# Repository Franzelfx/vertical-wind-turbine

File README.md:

# Vertical wind turbine

A small 3D-printed vertical-axis turbine on a timber post, charging a 3S Li-ion pack (the usual "12 V")
through its own electronics in a weatherproof box. Every part is generated by scripts from one file of
numbers.

> [!NOTE]
> **Digital design only.** The enclosure and drive train are modelled and pass collision checks. The
> schematic passes ERC, and the board is placed but not routed. There is no firmware. Nothing is built, and
> every power figure is an estimate. Next steps are in [plans/](plans/README.md).

<p align="center">
  
</p>

## What to expect

This is a project to enjoy, not an energy source.

<!-- vawt:key-figures:start -->
| Figure | Value |
| --- | --- |
| Rotor | 245 x 890 mm, printed in ASA |
| Post | 80 x 80 mm timber, 3 m tall |
| Battery | 3S2P Li-ion, 76 Wh, 9.0-12.6 V |
| Charges in winds of | 2.8 to 17.1 m/s |
| Best output | 19.1 W, at 17 m/s |
| Average output | 0.43 W at an assumed 3.5 m/s mean wind: 3.8 kWh a year |
| A 20 W solar panel, for scale | about 19 kWh a year |
| Requirements | 23 of 23 hold, on paper |
<!-- vawt:key-figures:end -->

Treat power figures as ±50 % until bench tests replace the assumptions: see
[sizing](docs/sizing.md), [assumptions](docs/assumptions.md) and [bench tests](plans/bench.md).

## How it works

```mermaid
flowchart LR
    wind([Wind]) --> rotor[Printed rotor]
    rotor --> generator[Gimbal motor<br/>as generator]
    generator --> guard[Bridge and<br/>overvoltage relay]
    guard --> charger[BQ25798<br/>charger]
    charger --> pack[(3S Li-ion<br/>pack)]
    pack --> load([Your load])
    mcu[ESP32-C3] -. tracks the best point .-> charger
```

The relay needs no battery and no firmware: the overvoltage itself opens it
([ADR-006](docs/decisions/ADR-006-overvoltage-relay.md)).

## Pictures

All are computer renders, and the garden is set dressing. Select one for full size.

| On its post | From the side | The rotor from below |
| --- | --- | --- |
|  |  |  |

| Upper bracket | Drive train | Cover off |
| --- | --- | --- |
|  |  |  |

| Enclosure | Inside | Exploded |
| --- | --- | --- |
|  |  |  |

## Documentation

| Page | What it holds |
| --- | --- |
| [Requirements](plans/requirements.md) | Numbered limits and where each stands |
| [Sizing](docs/sizing.md) | Power, yield, overvoltage, stopping, structure, vibration |
| [Assumptions](docs/assumptions.md) | Every number nobody has measured |
| [Hardware](docs/hardware.md), [printing](docs/printing.md), [board parts](docs/bom.md) | What to buy and print |
| [Schematic](docs/images/charge-board-schematic.pdf) | The charge board, as a PDF |
| [Decisions](docs/README.md#decisions) | Why it is the way it is, including which choices were made by AI |
| [Plans](plans/README.md) | Mechanical, electronics and bench tests, with what is done |

## Layout

```text
src/vawt/          spec.py: every number. system/: sizing, requirements. io/: docs, booklet, meshes
cad/freecad/       The parts and assembly, as FreeCAD Python
cad/vendor/        The licensed rotor, not in git
electronics/       KiCad: charge-board/ with its schematic as code, lib/ with project parts
firmware/          ESP32-C3, not started
tools/             run-checks, build-cad, build-electronics, render
report/            The booklet's text and layout, as Typst
tests/             Requirements, CAD report, ERC and DRC, doc integrity
plans/             Intent: requirements, mechanical, electronics, bench tests
docs/              State: generated pages, decisions, images
datasheets/        Parts' datasheets
bench/runs/        Raw logs from physical tests
build/             Generated: STEP, STL, FCStd, reports. Not committed
```

## Use

Needs [`uv`](https://docs.astral.sh/uv/), FreeCAD 1.1, KiCad 10 and Blender, each in its default place or
named by an environment variable ([CLAUDE.md](CLAUDE.md)). Git LFS holds the full-size renders and PDFs. For
the CAD build, put the rotor's 3MF in `cad/vendor/ugrinsky/` ([how](cad/vendor/ugrinsky/README.md)).

```sh
uv run vawt sizing          # the figures
tools/run-checks.sh         # everything, about 90 s
tools/render.sh             # the pictures, about 10 minutes (--samples 32 --width 800 for a draft)
uv run vawt pdf             # the booklet for friends: build/report/vertical-wind-turbine.pdf
```

Afterwards, `build/cad/wind-turbine.FCStd` opens in FreeCAD, `build/cad/` holds each part's STEP and STL, and
`electronics/charge-board/charge-board.kicad_pro` opens in KiCad. In FreeCAD, run
`cad/freecad/apply_colours.py` to colour the assembly. Change parts in the scripts, not in the generated
files ([ADR-001](docs/decisions/ADR-001-tools.md)).

## Safety

> [!WARNING]
> This has not been built, tested or certified.
>
> - **Not storm-proof unattended.** Fit the parking pin before forecast storms, and keep the fall zone clear
>   ([ADR-005](docs/decisions/ADR-005-storm-parking-pin.md)).
> - **A printed box does not contain a Li-ion fire** ([ADR-008](docs/decisions/ADR-008-enclosure.md)).
> - **The tips move fast.** Fit the pin before touching the rotor.

## Credits and licence

The rotor is GeoJolt's
["Ugrinsky Style wind Turbine"](https://makerworld.com/de/models/861294-ugrinsky-style-wind-turbine) from
MakerWorld, under its Standard Digital File License. GeoJolt holds the rights to that design, which appears in
the renders. Its files are not in this repository ([ADR-003](docs/decisions/ADR-003-rotor-licence.md)).

This project has no licence of its own yet, so its contents are not offered for reuse. The datasheets belong
to their makers.

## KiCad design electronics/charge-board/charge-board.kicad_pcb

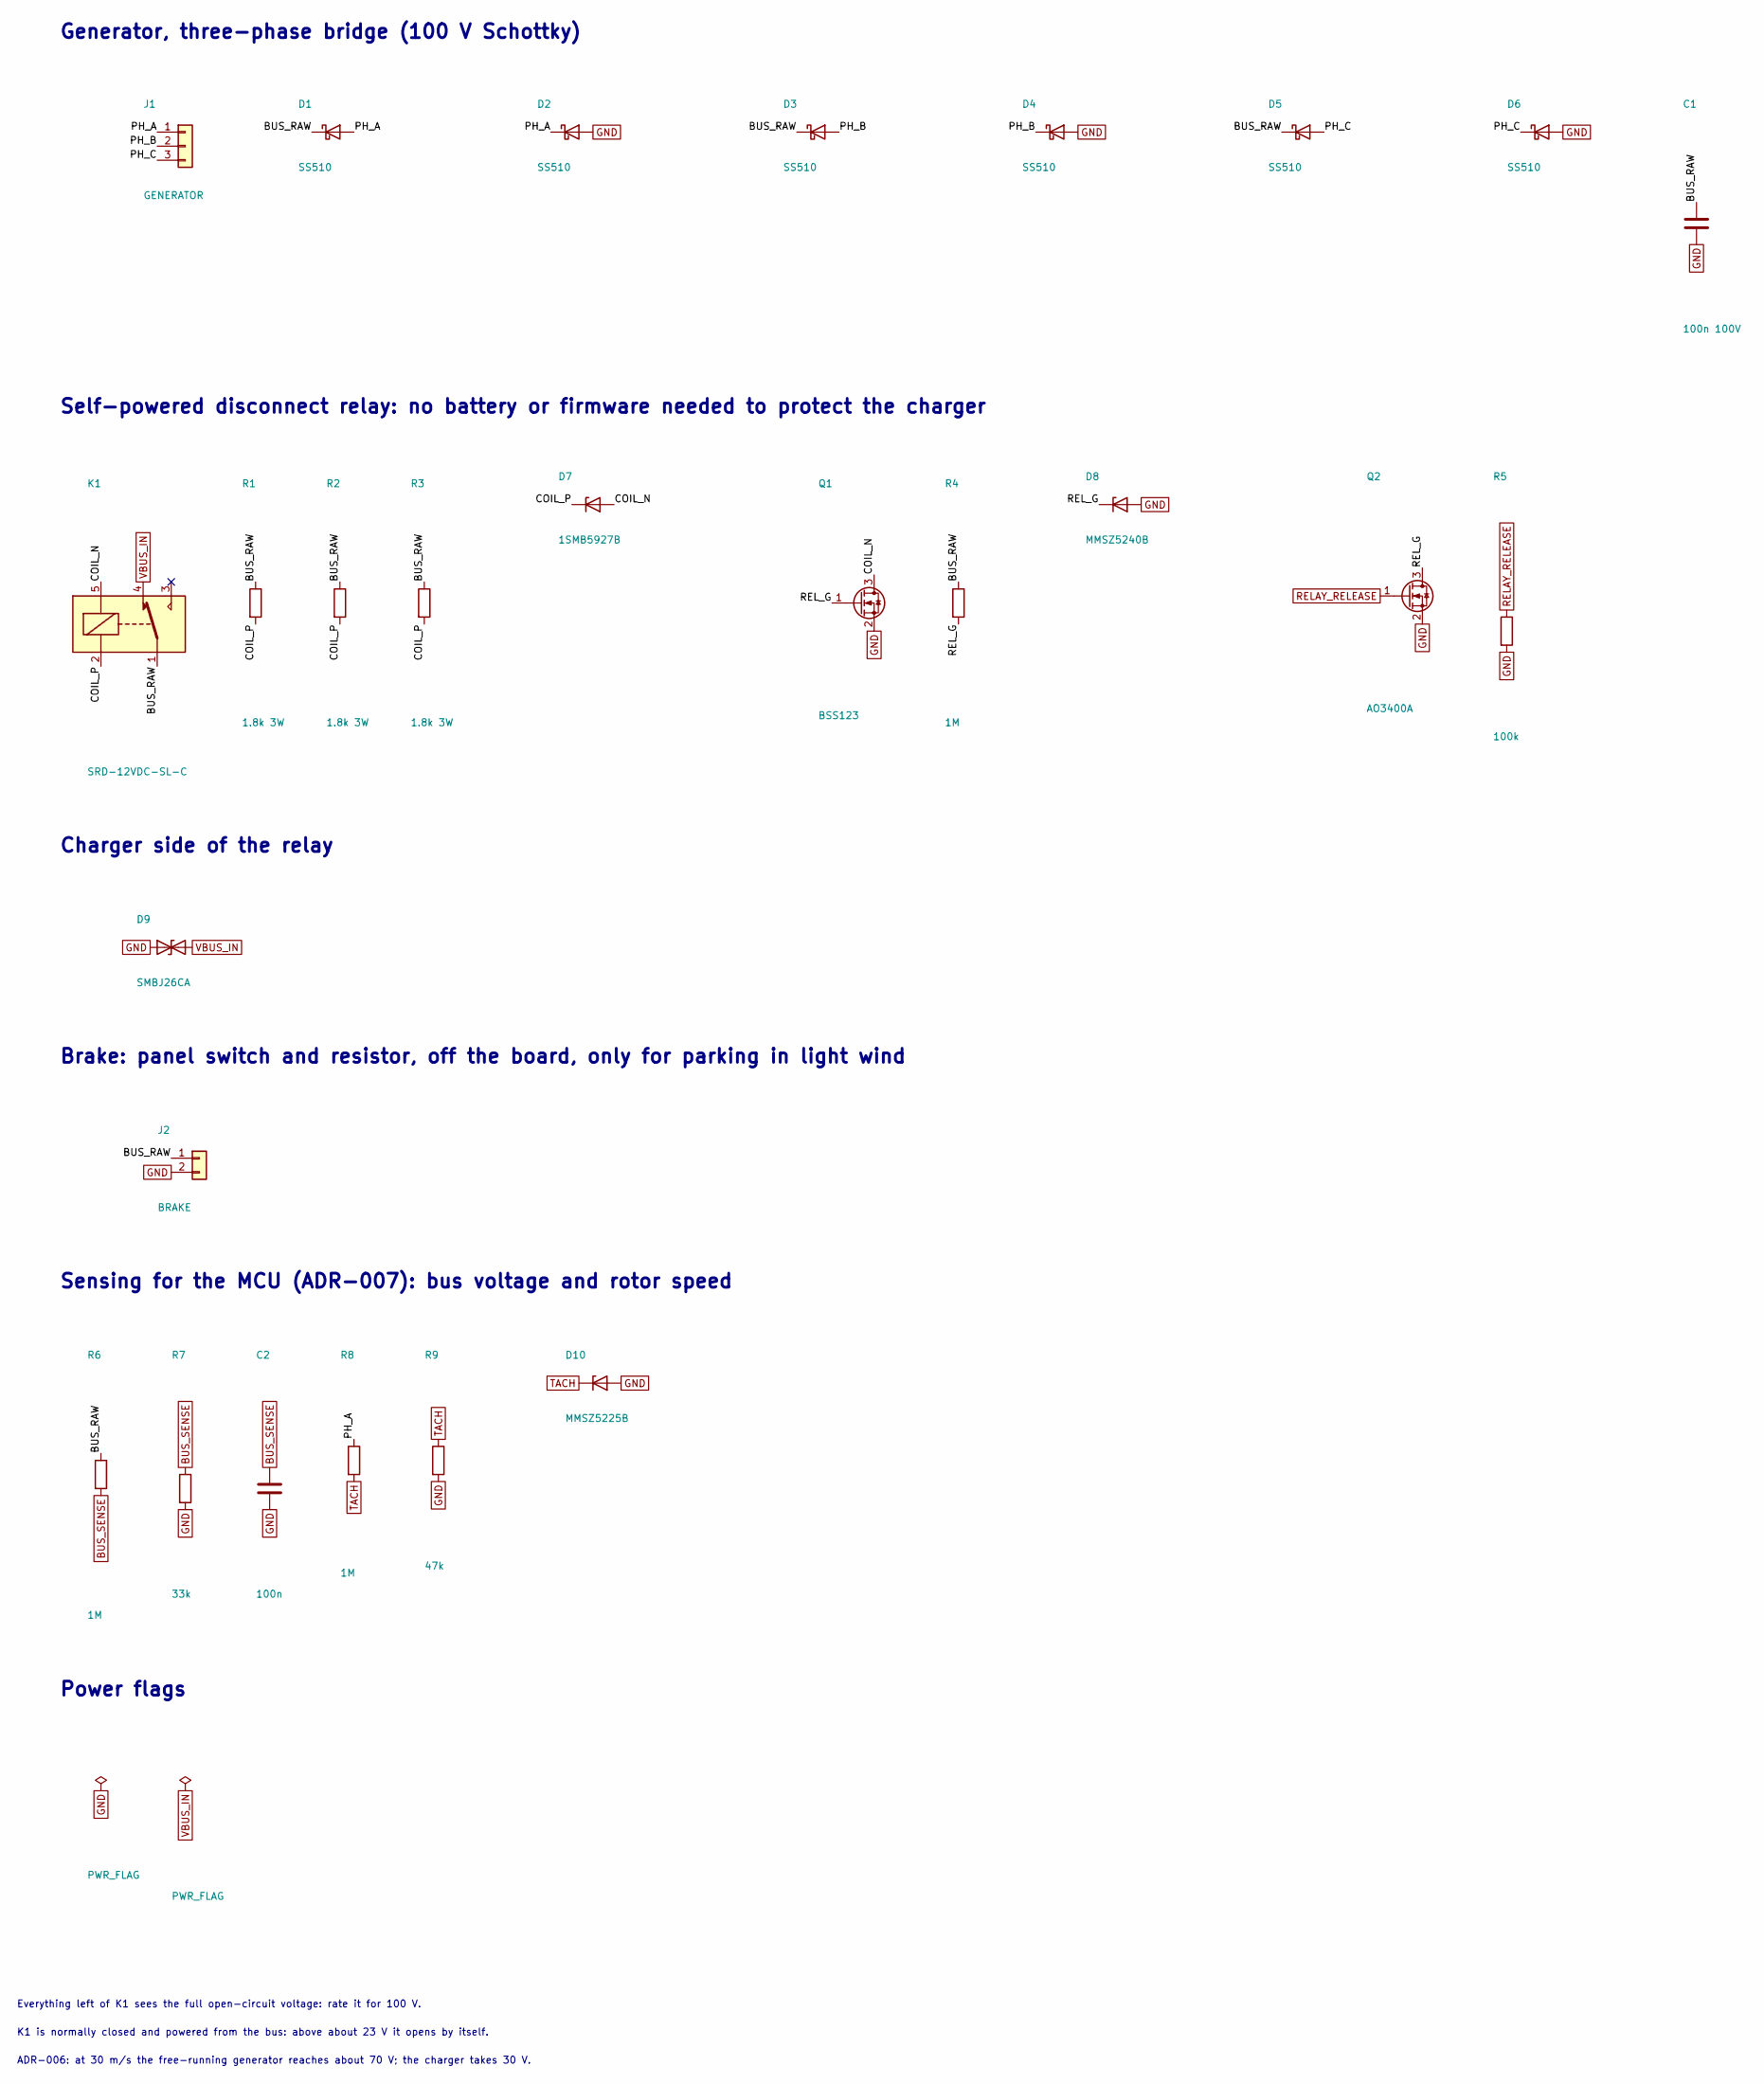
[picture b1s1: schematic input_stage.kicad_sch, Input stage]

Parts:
C1: 100n 100V; C_1206_3216Metric; LCSC Part C107181
C2: 100n; C_0603_1608Metric; LCSC Part C14663
D1, D2, D3, D4, D5, D6: SS510; D_SMC; LCSC Part C19229
D7: 1SMB5927B; D_SMB; LCSC Part C53171
D8: MMSZ5240B; D_SOD-123; LCSC Part C151060
D9: SMBJ26CA; D_SMB; LCSC Part C123932
D10: MMSZ5225B; D_SOD-123; LCSC Part C22399894
J1: GENERATOR; TerminalBlock_Phoenix_MKDS-1,5-3-5.08_1x03_P5.08mm_Horizont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; LCSC Part C474953
J2: BRAKE; TerminalBlock_Phoenix_MKDS-1,5-2-5.08_1x02_P5.08mm_Horizont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; LCSC Part C474952
K1: SRD-12VDC-SL-C; Relay_SPDT_SANYOU_SRD_Series_Form_C; LCSC Part C30431
Q1: BSS123; SOT-23; LCSC Part C78962
Q2: AO3400A; SOT-23; LCSC Part C20917
R1, R2, R3: 1.8k 3W; R_Axial_DIN0516_L15.5mm_D5.0mm_P20.32mm_Horizontal
R4, R6, R8: 1M; R_0603_1608Metric; LCSC Part C22935
R5: 100k; R_0603_1608Metric; LCSC Part C25803
R7: 33k; R_0603_1608Metric; LCSC Part C4216
R9: 47k; R_0603_1608Metric; LCSC Part C25819

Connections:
/Input stage/BUS_RAW: C1.1, D1.1 (K), D3.1 (K), D5.1 (K), J2.1, K1.1, R1.1, R2.1, R3.1, R4.1, R6.1
/Input stage/COIL_N: D7.2 (A), K1.5, Q1.3 (D)
/Input stage/COIL_P: D7.1 (K), K1.2, R1.2, R2.2, R3.2
/Input stage/PH_A: D1.2 (A), D2.1 (K), J1.1, R8.1
/Input stage/PH_B: D3.2 (A), D4.1 (K), J1.2
/Input stage/PH_C: D5.2 (A), D6.1 (K), J1.3
/Input stage/REL_G: D8.1 (K), Q1.1 (G), Q2.3 (D), R4.2
BUS_SENSE: C2.1, R6.2, R7.1; also elsewhere on the board
GND: C1.2, C2.2, D2.2 (A), D4.2 (A), D6.2 (A), D8.2 (A), D9.1 (A1), D10.2 (A), J2.2, Q1.2 (S), Q2.2 (S), R5.2, R7.2, R9.2; also elsewhere on the board
RELAY_RELEASE: Q2.1 (G), R5.1; also elsewhere on the board
TACH: D10.1 (K), R8.2, R9.1; also elsewhere on the board
VBUS_IN: D9.2 (A2), K1.4; also elsewhere on the board

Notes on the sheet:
Generator, three-phase bridge (100 V Schottky)
Self-powered disconnect relay: no battery or firmware needed to protect the charger
Charger side of the relay
Brake: panel switch and resistor, off the board, only for parking in light wind
Sensing for the MCU (ADR-007): bus voltage and rotor speed
Power flags
ADR-006: at 30 m/s the free-running generator reaches about 70 V; the charger takes 30 V.
K1 is normally closed and powered from the bus: above about 23 V it opens by itself.
Everything left of K1 sees the full open-circuit voltage: rate it for 100 V.

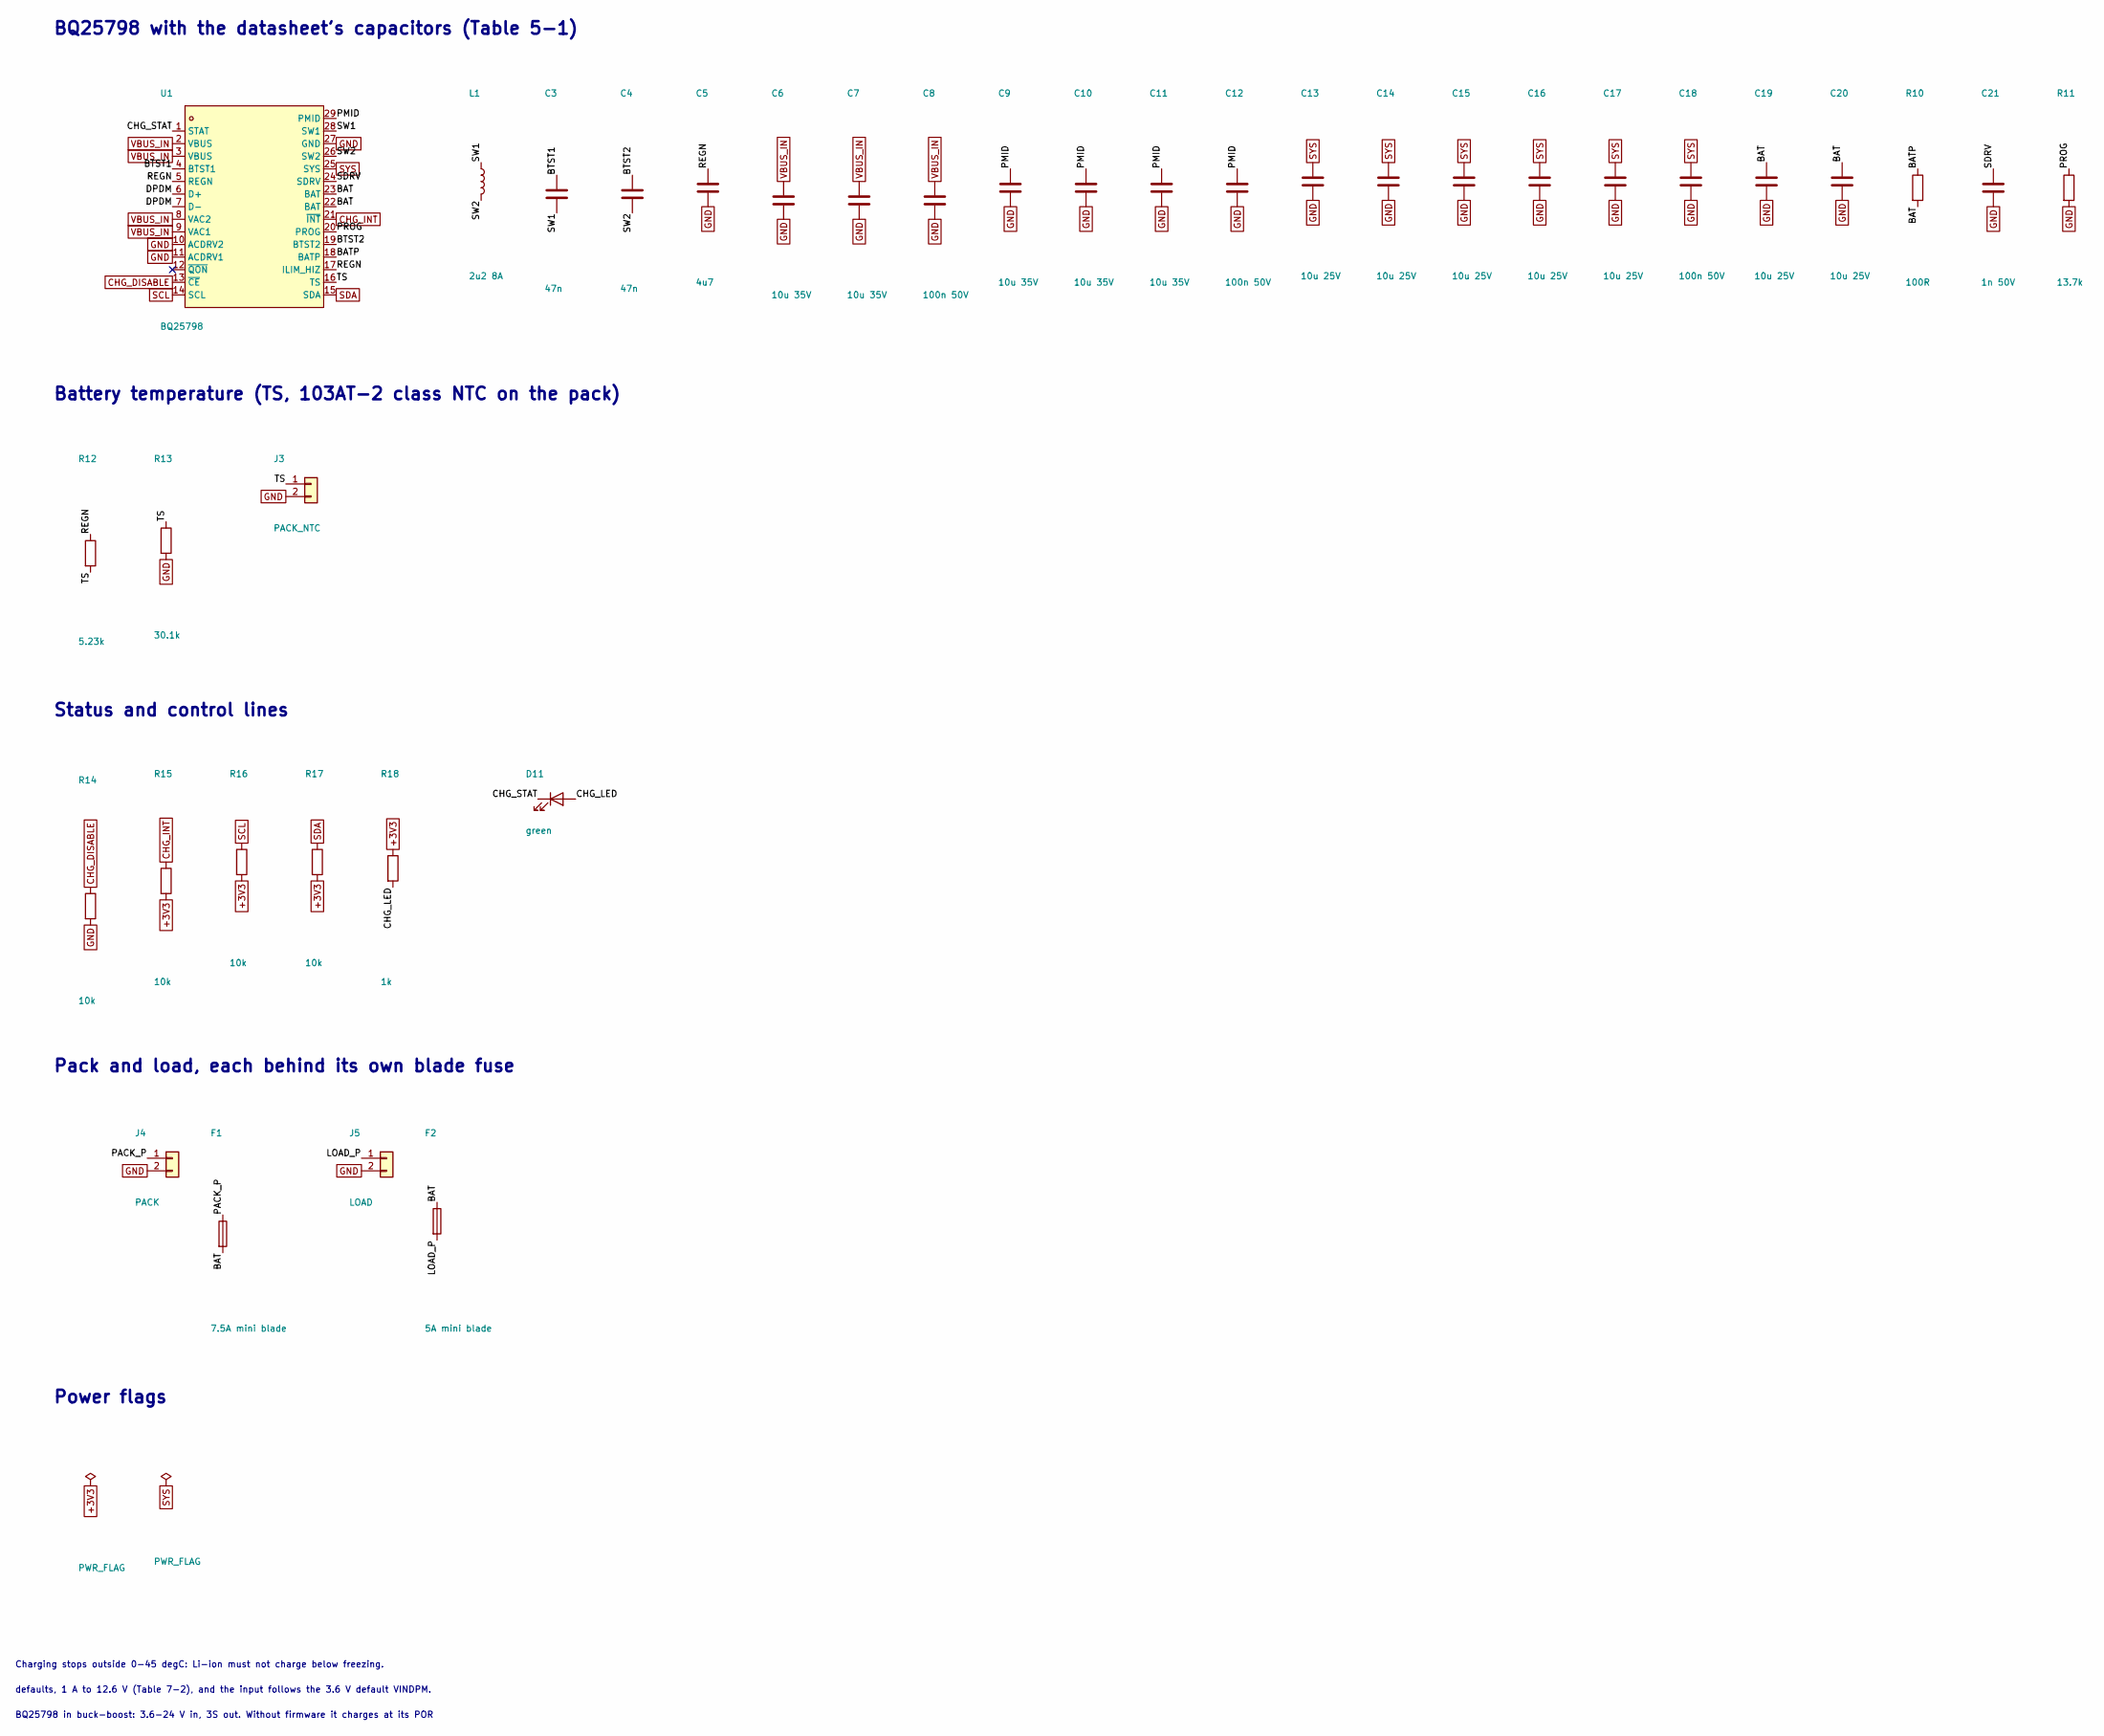
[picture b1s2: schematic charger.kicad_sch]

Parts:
C3, C4: 47n; C_0603_1608Metric; LCSC Part C107093
C5: 4u7; C_0603_1608Metric; LCSC Part C380325
C6, C7, C9, C10, C11: 10u 35V; C_1206_3216Metric; LCSC Part C6119957
C8, C12, C18: 100n 50V; C_0603_1608Metric; LCSC Part C14663
C13, C14, C15, C16, C17, C19, C20: 10u 25V; C_0805_2012Metric; LCSC Part C5448891
C21: 1n 50V; C_0603_1608Metric; LCSC Part C100040
D11: green; LED_0603_1608Metric; LCSC Part C12624
F1: 7.5A mini blade; Fuse_Blade_Mini_directSolder
F2: 5A mini blade; Fuse_Blade_Mini_directSolder
J3: PACK_NTC; JST_XH_B2B-XH-A_1x02_P2.50mm_Vertical; LCSC Part C158012
J4: PACK; TerminalBlock_Phoenix_MKDS-1,5-2-5.08_1x02_P5.08mm_Horizont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; LCSC Part C474952
J5: LOAD; TerminalBlock_Phoenix_MKDS-1,5-2-5.08_1x02_P5.08mm_Horizont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; LCSC Part C474952
L1: 2u2 8A; L_Sunlord_MWSA0518S; LCSC Part C408345
R10: 100R; R_0603_1608Metric; LCSC Part C22775
R11: 13.7k; R_0603_1608Metric; LCSC Part C22793
R12: 5.23k; R_0603_1608Metric; LCSC Part C23068
R13: 30.1k; R_0603_1608Metric; LCSC Part C23000
R14, R15, R16, R17: 10k; R_0603_1608Metric; LCSC Part C25804
R18: 1k; R_0603_1608Metric; LCSC Part C21190
U1: BQ25798; QFN-29_L4.0-W4.0-P0.40-TL-BQ25792RQMR; LCSC Part C2876593

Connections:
+3V3: R15.2, R16.2, R17.2, R18.1; also elsewhere on the board
/Charger/BAT: C19.1, C20.1, F1.2, F2.1, R10.2, U1.22 (BAT), U1.23 (BAT)
/Charger/BATP: R10.1, U1.18 (BATP)
/Charger/BTST1: C3.1, U1.4 (BTST1)
/Charger/BTST2: C4.1, U1.19 (BTST2)
/Charger/CHG_LED: D11.2 (A), R18.2
/Charger/CHG_STAT: D11.1 (K), U1.1 (STAT)
/Charger/DPDM: U1.6 (D+), U1.7 (D-)
/Charger/LOAD_P: F2.2, J5.1
/Charger/PACK_P: F1.1, J4.1
/Charger/PMID: C9.1, C10.1, C11.1, C12.1, U1.29 (PMID)
/Charger/PROG: R11.1, U1.20 (PROG)
/Charger/REGN: C5.1, R12.1, U1.5 (REGN), U1.17 (ILIM_HIZ)
/Charger/SDRV: C21.1, U1.24 (SDRV)
/Charger/SW1: C3.2, L1.1, U1.28 (SW1)
/Charger/SW2: C4.2, L1.2, U1.26 (SW2)
/Charger/TS: J3.1, R12.2, R13.1, U1.16 (TS)
CHG_DISABLE: R14.1, U1.13 (~CE); also elsewhere on the board
CHG_INT: R15.1, U1.21 (~INT); also elsewhere on the board
GND: C5.2, C6.2, C7.2, C8.2, C9.2, C10.2, C11.2, C12.2, C13.2, C14.2, C15.2, C16.2, C17.2, C18.2, C19.2, C20.2, C21.2, J3.2, J4.2, J5.2, R11.2, R13.2, R14.2, U1.10 (ACDRV2), U1.11 (ACDRV1), U1.27 (GND); also elsewhere on the board
SCL: R16.1, U1.14 (SCL); also elsewhere on the board
SDA: R17.1, U1.15 (SDA); also elsewhere on the board
SYS: C13.1, C14.1, C15.1, C16.1, C17.1, C18.1, U1.25 (SYS); also elsewhere on the board
VBUS_IN: C6.1, C7.1, C8.1, U1.2 (VBUS), U1.3 (VBUS), U1.8 (VAC2), U1.9 (VAC1); also elsewhere on the board

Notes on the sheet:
BQ25798 with the datasheet's capacitors (Table 5-1)
Battery temperature (TS, 103AT-2 class NTC on the pack)
Status and control lines
Pack and load, each behind its own blade fuse
Power flags
BQ25798 in buck-boost: 3.6-24 V in, 3S out. Without firmware it charges at its POR
defaults, 1 A to 12.6 V (Table 7-2), and the input follows the 3.6 V default VINDPM.
Charging stops outside 0-45 degC: Li-ion must not charge below freezing.

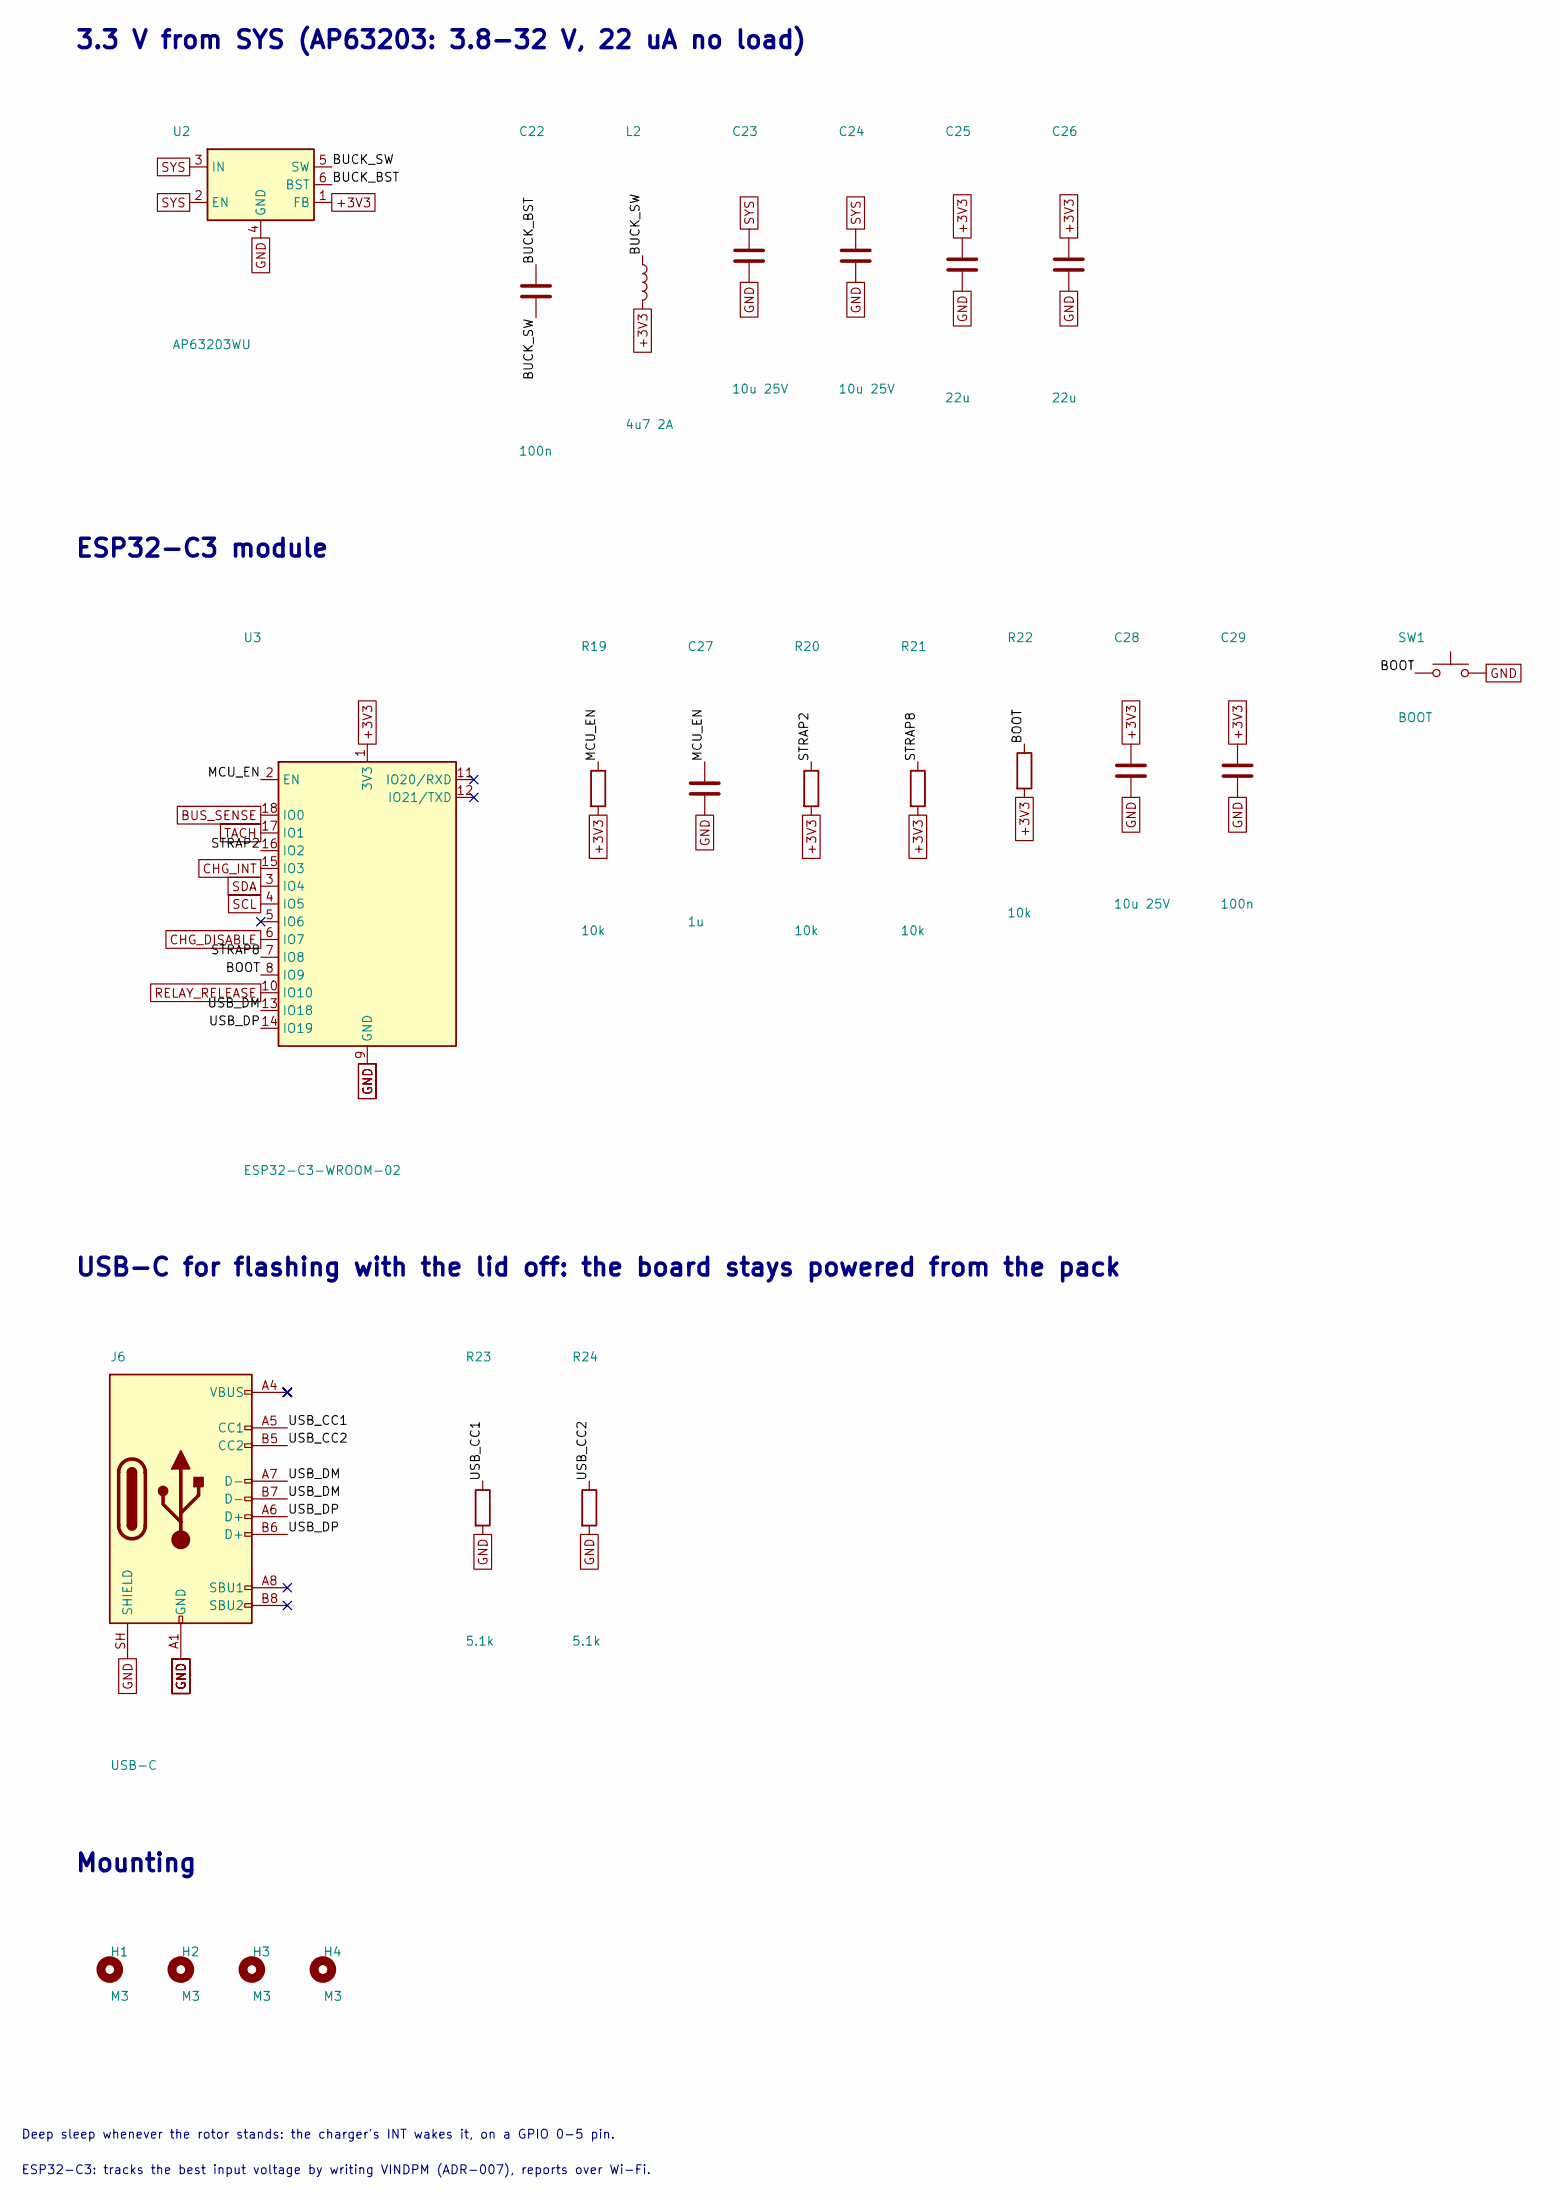
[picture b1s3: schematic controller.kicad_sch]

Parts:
C22, C29: 100n; C_0603_1608Metric; LCSC Part C14663
C23, C24, C28: 10u 25V; C_0805_2012Metric; LCSC Part C5448891
C25, C26: 22u; C_0805_2012Metric; LCSC Part C380336
C27: 1u; C_0603_1608Metric; LCSC Part C1592
H1, H2, H3, H4: M3; MountingHole_3.2mm_M3
J6: USB-C; USB_C_Receptacle_HRO_TYPE-C-31-M-12; LCSC Part C165948
L2: 4u7 2A; L_Sunlord_MWSA0402S; LCSC Part C408337
R19, R20, R21, R22: 10k; R_0603_1608Metric; LCSC Part C25804
R23, R24: 5.1k; R_0603_1608Metric; LCSC Part C23186
SW1: BOOT; SW_SPST_PTS645Sx43SMTR92; LCSC Part C221880
U2: AP63203WU; TSOT-23-6; LCSC Part C780769
U3: ESP32-C3-WROOM-02; LCSC Part C2934560

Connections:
+3V3: C25.1, C26.1, C28.1, C29.1, L2.2, R19.2, R20.2, R21.2, R22.2, U2.1 (FB), U3.1 (3V3); also elsewhere on the board
/Controller/BOOT: R22.1, SW1.1, U3.8 (IO9)
/Controller/BUCK_BST: C22.1, U2.6 (BST)
/Controller/BUCK_SW: C22.2, L2.1, U2.5 (SW)
/Controller/MCU_EN: C27.1, R19.1, U3.2 (EN)
/Controller/STRAP2: R20.1, U3.16 (IO2)
/Controller/STRAP8: R21.1, U3.7 (IO8)
/Controller/USB_CC1: J6.A5 (CC1), R23.1
/Controller/USB_CC2: J6.B5 (CC2), R24.1
/Controller/USB_DM: J6.A7 (D-), J6.B7 (D-), U3.13 (IO18)
/Controller/USB_DP: J6.A6 (D+), J6.B6 (D+), U3.14 (IO19)
BUS_SENSE: U3.18 (IO0); also elsewhere on the board
CHG_DISABLE: U3.6 (IO7); also elsewhere on the board
CHG_INT: U3.15 (IO3); also elsewhere on the board
GND: C23.2, C24.2, C25.2, C26.2, C27.2, C28.2, C29.2, J6.A1 (GND), J6.A12 (GND), J6.B1 (GND), J6.B12 (GND), J6.SH (SHIELD), R23.2, R24.2, SW1.2, U2.4 (GND), U3.9 (GND), U3.19 (GND); also elsewhere on the board
RELAY_RELEASE: U3.10 (IO10); also elsewhere on the board
SCL: U3.4 (IO5); also elsewhere on the board
SDA: U3.3 (IO4); also elsewhere on the board
SYS: C23.1, C24.1, U2.2 (EN), U2.3 (IN); also elsewhere on the board
TACH: U3.17 (IO1); also elsewhere on the board

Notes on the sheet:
3.3 V from SYS (AP63203: 3.8-32 V, 22 uA no load)
ESP32-C3 module
USB-C for flashing with the lid off: the board stays powered from the pack
Mounting
ESP32-C3: tracks the best input voltage by writing VINDPM (ADR-007), reports over Wi-Fi.
Deep sleep whenever the rotor stands: the charger's INT wakes it, on a GPIO 0-5 pin.

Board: 4 copper layers, 85 parts (0 on the bottom side), 44 nets, no tracks yet.

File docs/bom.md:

# Board parts

> Generated by `tools/bom.py` from the KiCad netlist and JLCPCB's public catalogue; do not edit by hand
> (`tests/test_electronics.py` fails when a part in the schematic is missing here).

Stock and prices as of 2026-11-06, single-unit tier.

**Parts total: about 11.83 USD per board**, without the fab, assembly, and what is listed below.
Datasheet checks so far: ADR-007.

| Parts | Qty | Value | LCSC | Manufacturer's part | Stock | Unit price (USD) | Line |
| --- | --- | --- | --- | --- | --- | --- | --- |
| C1 | 1 | 100n 100V | C107181 | CC1206KKX7R0BB104 | 68,519 | 0.0402 | 0.04 |
| C13 C14 C15 C16 C17 C19 C20 C23 C24 C28 | 10 | 10u 25V | C5448891 | TCC0805X5R106K250FT | 183,339 | 0.0290 | 0.29 |
| C12 C18 C2 C22 C29 C8 | 6 | 100n | C14663 | CC0603KRX7R9BB104 | 34,754,599 | 0.0093 | 0.06 |
| C21 | 1 | 1n 50V | C100040 | CC0603KRX7R9BB102 | 2,016,034 | 0.0085 | 0.01 |
| C25 C26 | 2 | 22u | C380336 | TCC0805X5R226K100FT | 79,273 | 0.0477 | 0.10 |
| C27 | 1 | 1u | C1592 | CL10A105KO8NNNC | 1,921,364 | 0.0109 | 0.01 |
| C3 C4 | 2 | 47n | C107093 | CC0603KRX7R9BB473 | 1,311,137 | 0.0083 | 0.02 |
| C5 | 1 | 4u7 | C380325 | TCC0603X5R475K160CT | 945,252 | 0.0109 | 0.01 |
| C10 C11 C6 C7 C9 | 5 | 10u 35V | C6119957 | CGA1206X5R106K350NT | 17,421 | 0.0878 | 0.44 |
| D1 D2 D3 D4 D5 D6 | 6 | SS510 | C19229 | SS510C | 24,495 | 0.1137 | 0.68 |
| D10 | 1 | MMSZ5225B | C22399894 | MMSZ5225B | 14,811 | 0.0190 | 0.02 |
| D11 | 1 | green | C12624 | KT-0603G | 348,198 | 0.0119 | 0.01 |
| D7 | 1 | 1SMB5927B | C53171 | 1SMB5927BT3G | 31,381 | 0.1377 | 0.14 |
| D8 | 1 | MMSZ5240B | C151060 | MMSZ5240B-7-F | 40,197 | 0.0277 | 0.03 |
| D9 | 1 | SMBJ26CA | C123932 | SMBJ26CA | 97,352 | 0.0398 | 0.04 |
| J1 | 1 | GENERATOR | C474953 | KF128-5.08-3P-AA | 17,624 | 0.3175 | 0.32 |
| J2 J4 J5 | 3 | BRAKE | C474952 | KF128-5.08-2P-AA | 74,170 | 0.1927 | 0.58 |
| J3 | 1 | PACK_NTC | C158012 | B2B-XH-A(LF)(SN) | 597,562 | 0.0408 | 0.04 |
| J6 | 1 | USB-C | C165948 | TYPE-C-31-M-12 | 322,268 | 0.1870 | 0.19 |
| K1 | 1 | SRD-12VDC-SL-C | C30431 | SRD-12VDC-SL-C | 177,893 | 0.4421 | 0.44 |
| L1 | 1 | 2u2 8A | C408345 | MWSA0518S-2R2MT | 1,977 | 0.1556 | 0.16 |
| L2 | 1 | 4u7 2A | C408337 | MWSA0402S-4R7MT | 39,284 | 0.1500 | 0.15 |
| Q1 | 1 | BSS123 | C78962 | BSS123,215 | 194,333 | 0.0392 | 0.04 |
| Q2 | 1 | AO3400A | C20917 | AO3400A | 1,077,046 | 0.0889 | 0.09 |
| R10 | 1 | 100R | C22775 | 0603WAF1000T5E | 9,237,668 | 0.0021 | 0.00 |
| R11 | 1 | 13.7k | C22793 | 0603WAF1372T5E | 57,455 | 0.0016 | 0.00 |
| R12 | 1 | 5.23k | C23068 | 0603WAF5231T5E | 37,334 | 0.0020 | 0.00 |
| R13 | 1 | 30.1k | C23000 | 0603WAF3012T5E | 36,156 | 0.0016 | 0.00 |
| R14 R15 R16 R17 R19 R20 R21 R22 | 8 | 10k | C25804 | 0603WAF1002T5E | 42,888,502 | 0.0024 | 0.02 |
| R18 | 1 | 1k | C21190 | 0603WAF1001T5E | 27,627,900 | 0.0017 | 0.00 |
| R23 R24 | 2 | 5.1k | C23186 | 0603WAF5101T5E | 20,424,142 | 0.0015 | 0.00 |
| R4 R6 R8 | 3 | 1M | C22935 | 0603WAF1004T5E | 4,463,341 | 0.0018 | 0.01 |
| R5 | 1 | 100k | C25803 | 0603WAF1003T5E | 16,284,196 | 0.0029 | 0.00 |
| R7 | 1 | 33k | C4216 | 0603WAF3302T5E | 3,066,011 | 0.0021 | 0.00 |
| R9 | 1 | 47k | C25819 | 0603WAF4702T5E | 3,025,518 | 0.0016 | 0.00 |
| SW1 | 1 | BOOT | C221880 | PTS645SM43SMTR92LFS | 1,961 | 0.3766 | 0.38 |
| U1 | 1 | BQ25798 | C2876593 | BQ25798RQMR | 9,025 | 2.8682 | 2.87 |
| U2 | 1 | AP63203WU | C780769 | AP63203WU-7 | 5,619 | 1.3457 | 1.35 |
| U3 | 1 | ESP32-C3-WROOM-02 | C2934560 | ESP32-C3-WROOM-02-N4 | 13,503 | 3.3118 | 3.31 |

## Not at JLCPCB

Hand-fitted, from a distributor. Fuse holders are still open (`plans/electronics.md`, E2).

| Parts | Qty | Value | Footprint |
| --- | --- | --- | --- |
| F1 | 1 | 7.5A mini blade | Fuse_Blade_Mini_directSolder |
| F2 | 1 | 5A mini blade | Fuse_Blade_Mini_directSolder |
| R1 R2 R3 | 3 | 1.8k 3W | R_Axial_DIN0516_L15.5mm_D5.0mm_P20.32mm_Horizontal |

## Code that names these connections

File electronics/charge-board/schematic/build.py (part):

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        "J",
        "GENERATOR",
        BLOCK3,
        {"Pin_1": "PH_A", "Pin_2": "PH_B", "Pin_3": "PH_C"},
    )
    for phase in ("PH_A", "PH_B", "PH_C"):
        schottky(s, "SS510", phase, "BUS_RAW")
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    )

    s.section("Brake: panel switch and resistor, off the board, only for parking in light wind")
    s.part("Connector_Generic:Conn_01x02", "J", "BRAKE", BLOCK2, {"Pin_1": "BUS_RAW", "Pin_2": GND})

    s.section("Sensing for the MCU (ADR-007): bus voltage and rotor speed")
    R(s, "1M", "BUS_RAW", "BUS_SENSE")
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    s.part("Device:LED", "D", "green", LED, {"A": "CHG_LED", "K": "CHG_STAT"})

    s.section("Pack and load, each behind its own blade fuse")
    s.part("Connector_Generic:Conn_01x02", "J", "PACK", BLOCK2, {"Pin_1": "PACK_P", "Pin_2": GND})
    s.part("Device:Fuse", "F", f"{BATTERY.fuse_a}A mini blade", FUSE, {"1": "PACK_P", "2": "BAT"})
    s.part("Connector_Generic:Conn_01x02", "J", "LOAD", BLOCK2, {"Pin_1": "LOAD_P", "Pin_2": GND})
    s.part("Device:Fuse", "F", "5A mini blade", FUSE, {"1": "BAT", "2": "LOAD_P"})
    return s

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            "IO0": "BUS_SENSE",  # ADC1
            "IO1": "TACH",
            "IO2": "STRAP2",
            "IO3": "CHG_INT",  # wake source, deep sleep only wakes on GPIO 0-5
            "IO4": "SDA",
            "IO5": "SCL",
            "IO6": NC,
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
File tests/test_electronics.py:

"""The schematic and board, read from what KiCad reports. Needs `tools/build-electronics.sh`."""

import json
import re
import xml.etree.ElementTree as ET
from pathlib import Path

import pytest

from vawt.spec import BATTERY, BOARD, CHARGER, PROTECTION

ROOT = Path(__file__).resolve().parents[1]
BOARD_DIR = ROOT / "electronics" / "charge-board"
REPORTS = ROOT / "build" / "reports"
NETLIST = ROOT / "build" / "kicad" / "charge-board.net.xml"


@pytest.fixture(scope="module")
def net():
    if not NETLIST.exists():
        pytest.fail("no netlist: run tools/build-electronics.sh")
    root = ET.parse(NETLIST).getroot()
    comps = {c.get("ref"): c.findtext("value") for c in root.find("components")}
    pins = {}
    for n in root.find("nets"):
        for node in n:
            pins[(node.get("ref"), node.get("pin"))] = n.get("name").split("/")[-1]
    return comps, pins


def _ref(comps, value):
    return next(ref for ref, v in comps.items() if v == value)


def test_erc_is_clean():
    report = json.loads((REPORTS / "erc.json").read_text())
    errors = [v for sheet in report["sheets"] for v in sheet["violations"]]
    assert not errors, errors


def test_drc_is_clean_apart_from_open_connections():
    report = json.loads((REPORTS / "drc.json").read_text())
    assert report["violations"] == []
    assert report["schematic_parity"] == [], "board and schematic disagree"


def test_charger_is_programmed_for_3s(net):
    comps, pins = net
    prog = next(n for key, n in pins.items() if n == "PROG" and key[0].startswith("R"))
    assert prog == "PROG"
    r = next(key[0] for key, n in pins.items() if n == "PROG" and key[0].startswith("R"))
    assert comps[r] == f"{CHARGER.prog_ohm / 1000:.1f}k"
    assert CHARGER.cells == BATTERY.cells_series


def test_relay_common_is_the_bus_and_normally_closed_feeds_the_charger(net):
    comps, pins = net
    k = _ref(comps, "SRD-12VDC-SL-C")
    assert pins[(k, "1")] == "BUS_RAW"
    assert pins[(k, "4")] == "VBUS_IN"
    assert (k, "3") not in pins or pins[(k, "3")].startswith("unconnected")


def test_relay_series_resistors_match_the_spec(net):
    comps, pins = net
    series = [ref for ref, v in comps.items() if v.endswith("3W") and ref.startswith("R")]
    assert len(series) == 3
    each = float(comps[series[0]].split("k")[0]) * 1000
    assert each / 3 == pytest.approx(PROTECTION.relay_series_ohm)
    for ref in series:
        assert {pins[(ref, "1")], pins[(ref, "2")]} == {"BUS_RAW", "COIL_P"}


def test_every_terminal_in_the_spec_exists_in_the_schematic(net):
    comps, _ = net
    values = set(comps.values())
    for name, _x in BOARD.terminals:
        assert name in values, name


def test_tvs_protects_the_charger_side_only(net):
    comps, pins = net
    d = _ref(comps, "SMBJ26CA")
    assert "VBUS_IN" in {pins[(d, "1")], pins[(d, "2")]}


def test_mcu_can_wake_on_the_charger_interrupt(net):
    """ESP32-C3 deep sleep only wakes on GPIO 0-5."""
    comps, pins = net
    u = _ref(comps, "ESP32-C3-WROOM-02")
    assert pins[(u, "15")] == "CHG_INT"  # IO3


def test_board_outline_matches_the_spec():
    text = (BOARD_DIR / "charge-board.kicad_pcb").read_text()
    segments = re.findall(
        r"\(gr_line\s+\(start ([-\d.]+) ([-\d.]+)\)\s+\(end ([-\d.]+) ([-\d.]+)\)"
        r".*?\(layer \"Edge\.Cuts\"\)",
        text,
        re.DOTALL,
    )
    assert len(segments) == 4
    xs = [float(v) for s in segments for v in (s[0], s[2])]
    ys = [float(v) for s in segments for v in (s[1], s[3])]
    assert max(xs) - min(xs) == pytest.approx(BOARD.width)
    assert max(ys) - min(ys) == pytest.approx(BOARD.height)


def test_generated_schematic_is_not_hand_edited():
    """Regeneration gives identical files: UUIDs derive from references, so a diff is real."""
    before = {p.name: p.read_text() for p in BOARD_DIR.glob("*.kicad_sch")}
    assert len(before) == 4
    import subprocess
    import sys

    subprocess.run(
        [sys.executable, str(BOARD_DIR / "schematic" / "build.py")], check=True, capture_output=True
    )
    after = {p.name: p.read_text() for p in BOARD_DIR.glob("*.kicad_sch")}
    assert before == after


def test_bq25798_symbol_matches_the_datasheet_pinout():
    """Independent expected values: typed from SLUSDV2C Table 5-1, not read from the symbol."""
    table_5_1 = {
        "STAT": ["1"], "VBUS": ["2", "3"], "BTST1": ["4"], "REGN": ["5"], "D+": ["6"], "D-": ["7"],
        "VAC2": ["8"], "VAC1": ["9"], "ACDRV2": ["10"], "ACDRV1": ["11"], "~{QON}": ["12"],
        "~{CE}": ["13"], "SCL": ["14"], "SDA": ["15"], "TS": ["16"], "ILIM_HIZ": ["17"],
        "BATP": ["18"], "BTST2": ["19"], "PROG": ["20"], "~{INT}": ["21"], "BAT": ["22", "23"],
        "SDRV": ["24"], "SYS": ["25"], "SW2": ["26"], "GND": ["27"], "SW1": ["28"], "PMID": ["29"],
    }  # fmt: skip
    text = (ROOT / "electronics" / "lib" / "symbols" / "vawt.kicad_sym").read_text()
    found: dict[str, list[str]] = {}
    for name, number in re.findall(r'\(name "([^"]+)".*?\(number "(\d+)"', text, re.DOTALL):
        found.setdefault(name, []).append(number)
    assert {k: sorted(v, key=int) for k, v in found.items()} == table_5_1


def test_bom_snapshot_lists_every_part(net):
    comps, _ = net
    page = (ROOT / "docs" / "bom.md").read_text()
    listed = set(re.findall(r"\b[A-Z]+\d+\b", page))
    for ref in comps:
        if not ref.startswith("H"):  # mounting holes are not parts
            assert ref in listed, f"{ref}: run tools/bom.py"


def test_bom_snapshot_has_no_part_out_of_stock():
    page = (ROOT / "docs" / "bom.md").read_text()
    assert "**none**" not in page, "a part is out of stock: choose another"
